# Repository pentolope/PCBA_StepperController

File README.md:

# Quiet Stepper Motor Controller

Single-axis stepper controller using a modern quiet microstepping driver and a small MCU, from a 12–24 V supply at 1.5 A RMS/phase minimum.

`PCBA_StepperController` is a single-axis stepper motor controller built around a modern quiet microstepping driver (the brief offers "a Trinamic-class device" as an example, not a mandate) and a small MCU. The brief fixes the supply range (12–24 V), the phase current target (1.5 A RMS/phase minimum), the presence of current-sense resistors and bulk/ceramic decoupling, STEP/DIR plus UART/SPI configuration access, fault/status signals, and a 4-pin motor connector; it also directs specific attention to driver thermal-pad grounding, high-current phase loops, and keeping current-sense routing away from switching nodes. Everything else — the actual driver and MCU parts, the logic rail, sense-resistor values, connector families, board outline, stackup details, protection and thermal strategy — is left to the design agent. At detail 3/5 this is a mid-specificity brief: the electrical envelope and the layout hazards are named, the implementation is not.

> **This board has not been designed.** There is no schematic, no layout and no
> part selection here — only the brief, a reading of the brief, and the
> scaffolding a design run needs. That is the intended state of this repository,
> not a gap in it.

## What the brief fixes, and what it leaves open

The brief pins down 16 requirements and deliberately leaves
19 decisions to whoever designs the board. The `Source` column says
which is which: `brief` is quoted from [BRIEF.md](BRIEF.md), `metadata` comes
from the benchmark catalogue, and `open` means the brief does not fix it.

| Aspect | Value | Source |
|---|---|---|
| Function | Single-axis stepper controller | brief |
| Motor driver | A modern quiet microstepping driver; a Trinamic-class device is given as an example only, not a mandated part | brief |
| Controller | A small MCU on the board | brief |
| Input supply | 12–24 V | brief |
| Motor current target | 1.5 A RMS/phase minimum | brief |
| Sensing and decoupling | Current-sense resistors plus bulk/ceramic decoupling (values and technologies not fixed) | brief |
| Control and configuration interfaces | STEP/DIR, and UART/SPI configuration access | brief |
| Fault/status | Fault/status signals present (form not fixed) | brief |
| Motor connector | 4-pin (family, pitch and rating not fixed) | brief |
| Layout emphasis called out by the brief | Driver thermal-pad grounding, high-current phase loops, current-sense routing kept away from switching nodes | brief |
| Likely layer count | 4 preferred | metadata |
| Category / difficulty / brief detail | motor-control, difficulty 3, detail 3 | metadata |
| Primary stressors | motor-current routing, driver thermal pad, sense resistors, mixed-signal grounding | metadata |
| Board outline, size, mounting and power-input connector | Not fixed by the brief — design agent's choice | open |

The full split, with the verbatim brief text substantiating every fixed
requirement, is in [board/requirements.md](board/requirements.md) and
machine-readably in [board/requirements.json](board/requirements.json).

**Missing details are design freedom, not permission to fabricate unstated user
requirements.** A choice the brief left open is recorded as a decision, with its
reasoning — never promoted into a requirement.

## Benchmark position

| | |
|---|---|
| Benchmark id | 8 of 32 |
| Category | motor-control |
| Difficulty | 3 / 5 |
| Brief detail | 3 / 5 |
| Likely layer count | 4 preferred |
| Primary stressors | motor-current routing, driver thermal pad, sense resistors, mixed-signal grounding |

This is a motor-control board at difficulty 3/5 and detail 3/5: it tests whether an agent can carry a modest power stage from a stated current and supply envelope through conductor sizing, sense-resistor design and a defensible thermal path, rather than drawing a schematic that only looks right. The four named stressors — motor-current routing, driver thermal pad, sense resistors, mixed-signal grounding — are all layout-and-substantiation problems, so what separates a strong result from a plausible-looking one is whether the physical implementation and its supporting calculations agree. Because the brief names an example device class rather than a part, it also probes whether the agent treats an illustrative example as a requirement.

This repository is one of thirty-two. The suite, the protocol and the results
live in [PCBA_AutoDesignAndTest_Bench](https://github.com/pentolope/PCBA_AutoDesignAndTest_Bench).

## Repository layout

| Path | Contents |
|---|---|
| `BRIEF.md` | the supplied brief — authoritative, preserved byte for byte, never edited |
| `board/requirements.md` | what the brief fixes, what it leaves open, and where decisions get recorded |
| `board/requirements.json` | the same split, machine-readable, each fixed requirement bound to brief text |
| `board/manifest.template.json` | the toolkit's minimum manifest, pre-filled for this board |
| `board/toolchain.json` | where this board's build finds KiCad and the router |
| `benchmark/metadata.json` | the supplied catalogue entry — category, difficulty, detail, stressors |
| `docs/architecture.md` | the decisions this board must make, as questions, unanswered |
| `docs/sources.md` | the classes of evidence the design will have to cite |
| `docs/status.md` | what exists, what does not, and what is deliberately absent |
| `candidates/` | disposable search output, ignored by Git |
| `.claude/skills/` | the accountability-review skill [CLAUDE.md](CLAUDE.md) requires before a push |
| `tooling/PCBA_AutoDesignAndTest` | the shared verification/routing/release toolkit, as a pinned submodule |

## Getting the repository

The toolkit is a submodule and carries KiCad Routing Tools as a submodule of its
own, so clone recursively:

```bash
git clone --recursive https://github.com/pentolope/PCBA_StepperController.git
```

```bash
git submodule update --init --recursive
```

## Designing the board

Generic verification, routing and release logic is **not** written here. It is
consumed from `tooling/PCBA_AutoDesignAndTest`, which is board-agnostic by
construction and must stay that way; this repository owns the board and nothing
else. Start from
[the toolkit's onboarding guide](tooling/PCBA_AutoDesignAndTest/examples/onboarding.md),
and see [CLAUDE.md](CLAUDE.md) for the rules a design run works under.

```bash
python3 tooling/PCBA_AutoDesignAndTest/run.py preflight
```

## Brief integrity

`BRIEF.md` SHA-256 `eb32e622a2161815c687ef267615287b89c1135211a0c5d5494930910a460444`

Every quotation in `board/requirements.json` is bound to those exact bytes. If
the brief ever changes, the bindings are stale by construction — which is the
point of recording the digest.

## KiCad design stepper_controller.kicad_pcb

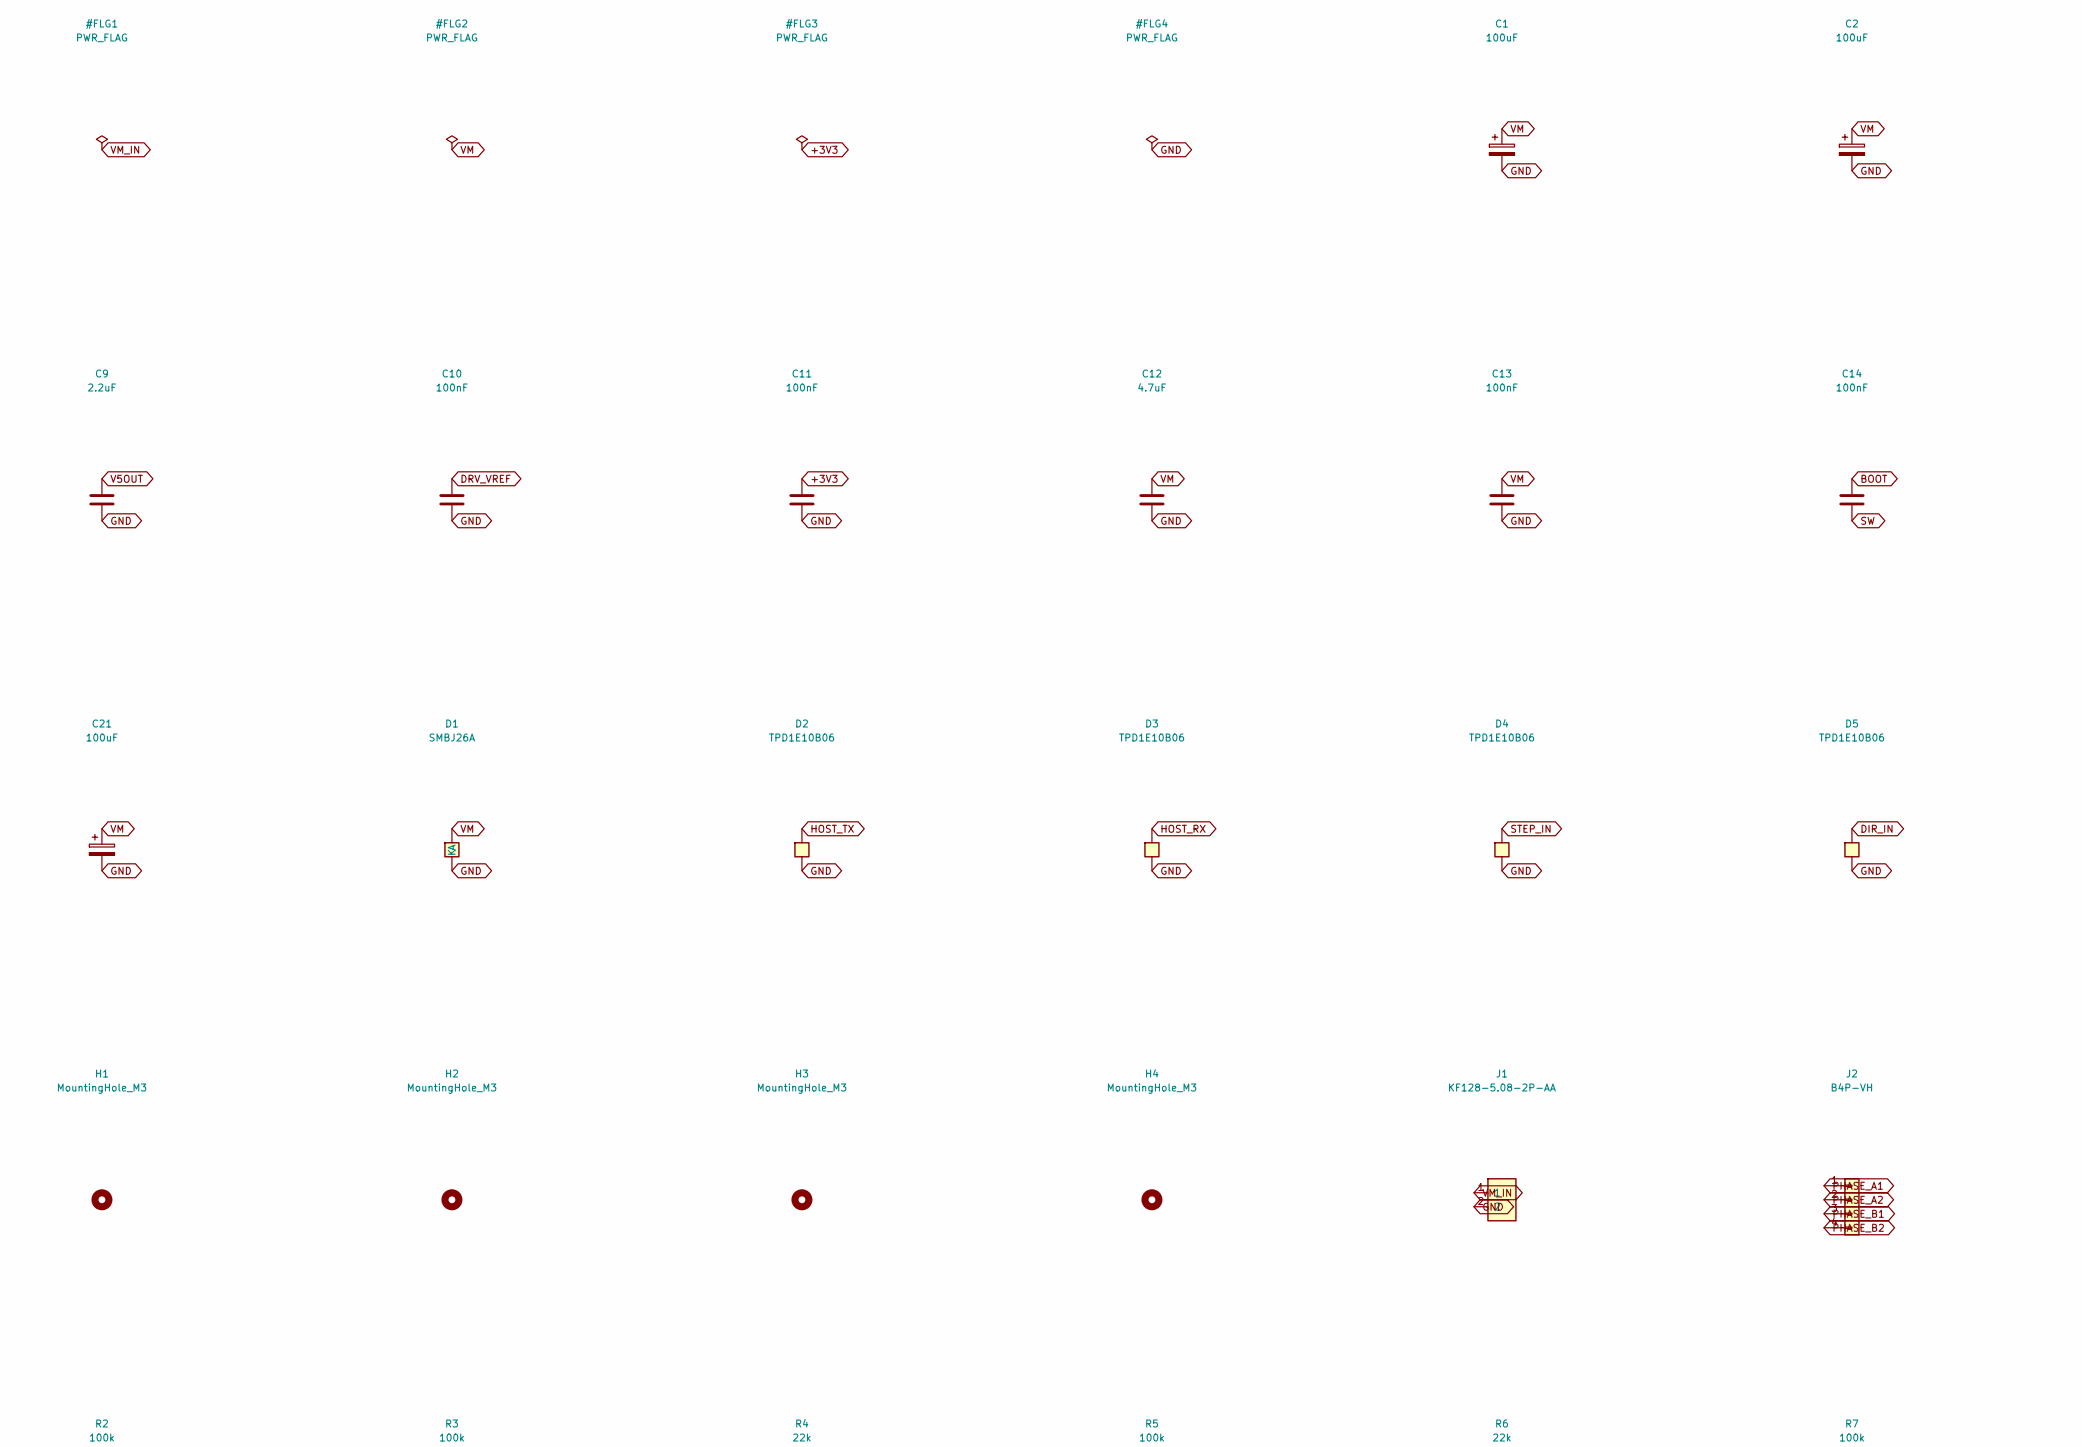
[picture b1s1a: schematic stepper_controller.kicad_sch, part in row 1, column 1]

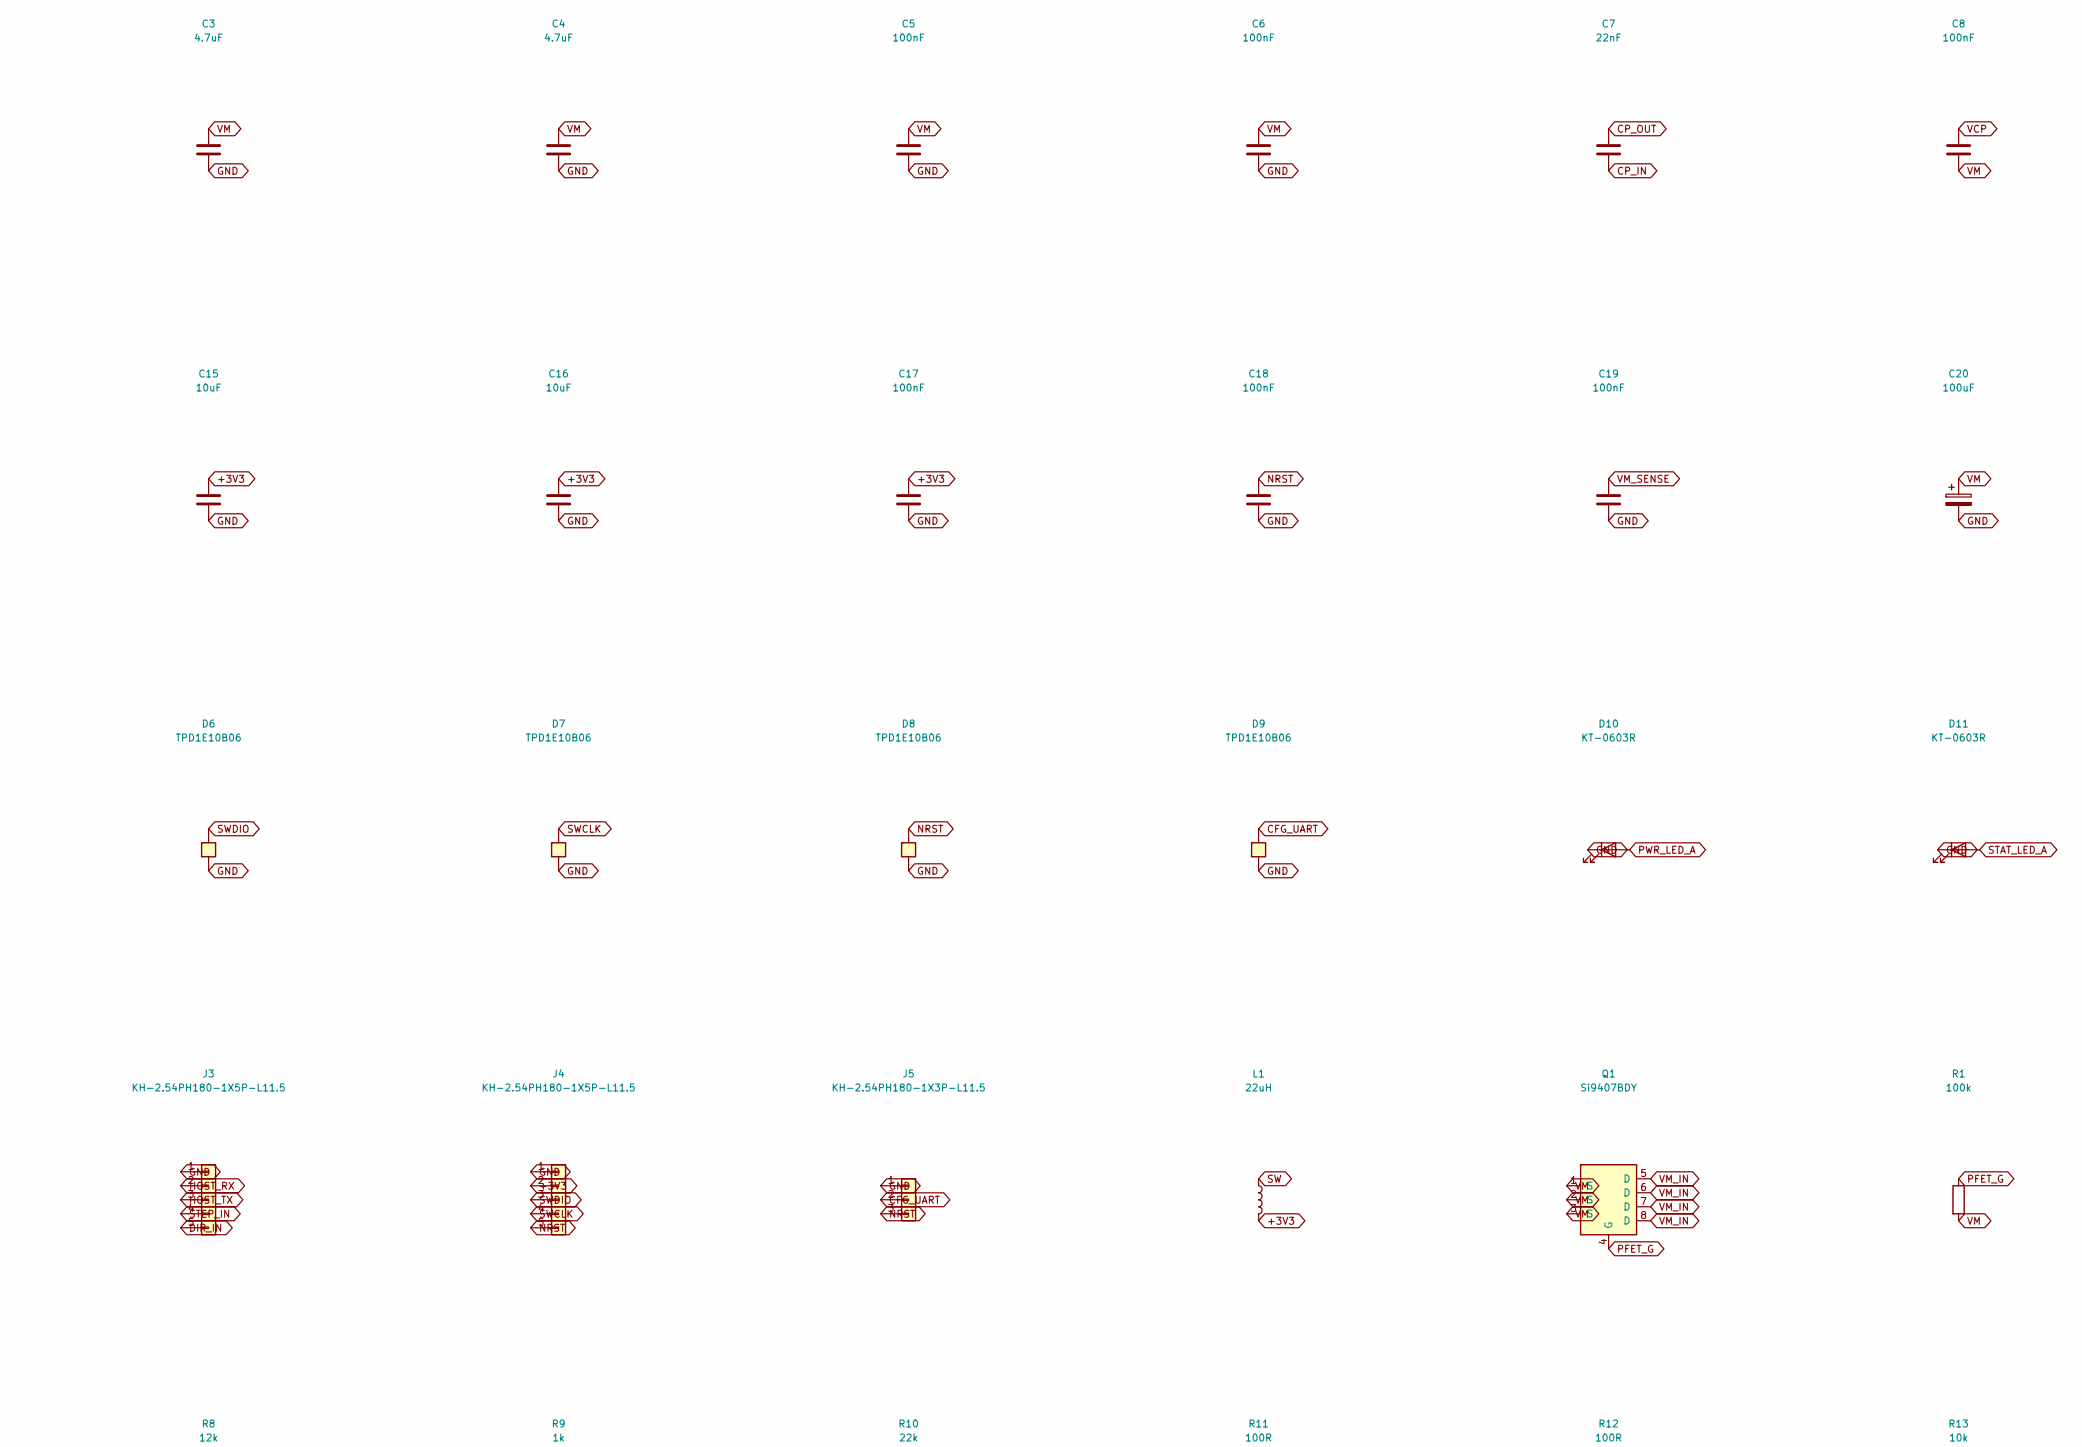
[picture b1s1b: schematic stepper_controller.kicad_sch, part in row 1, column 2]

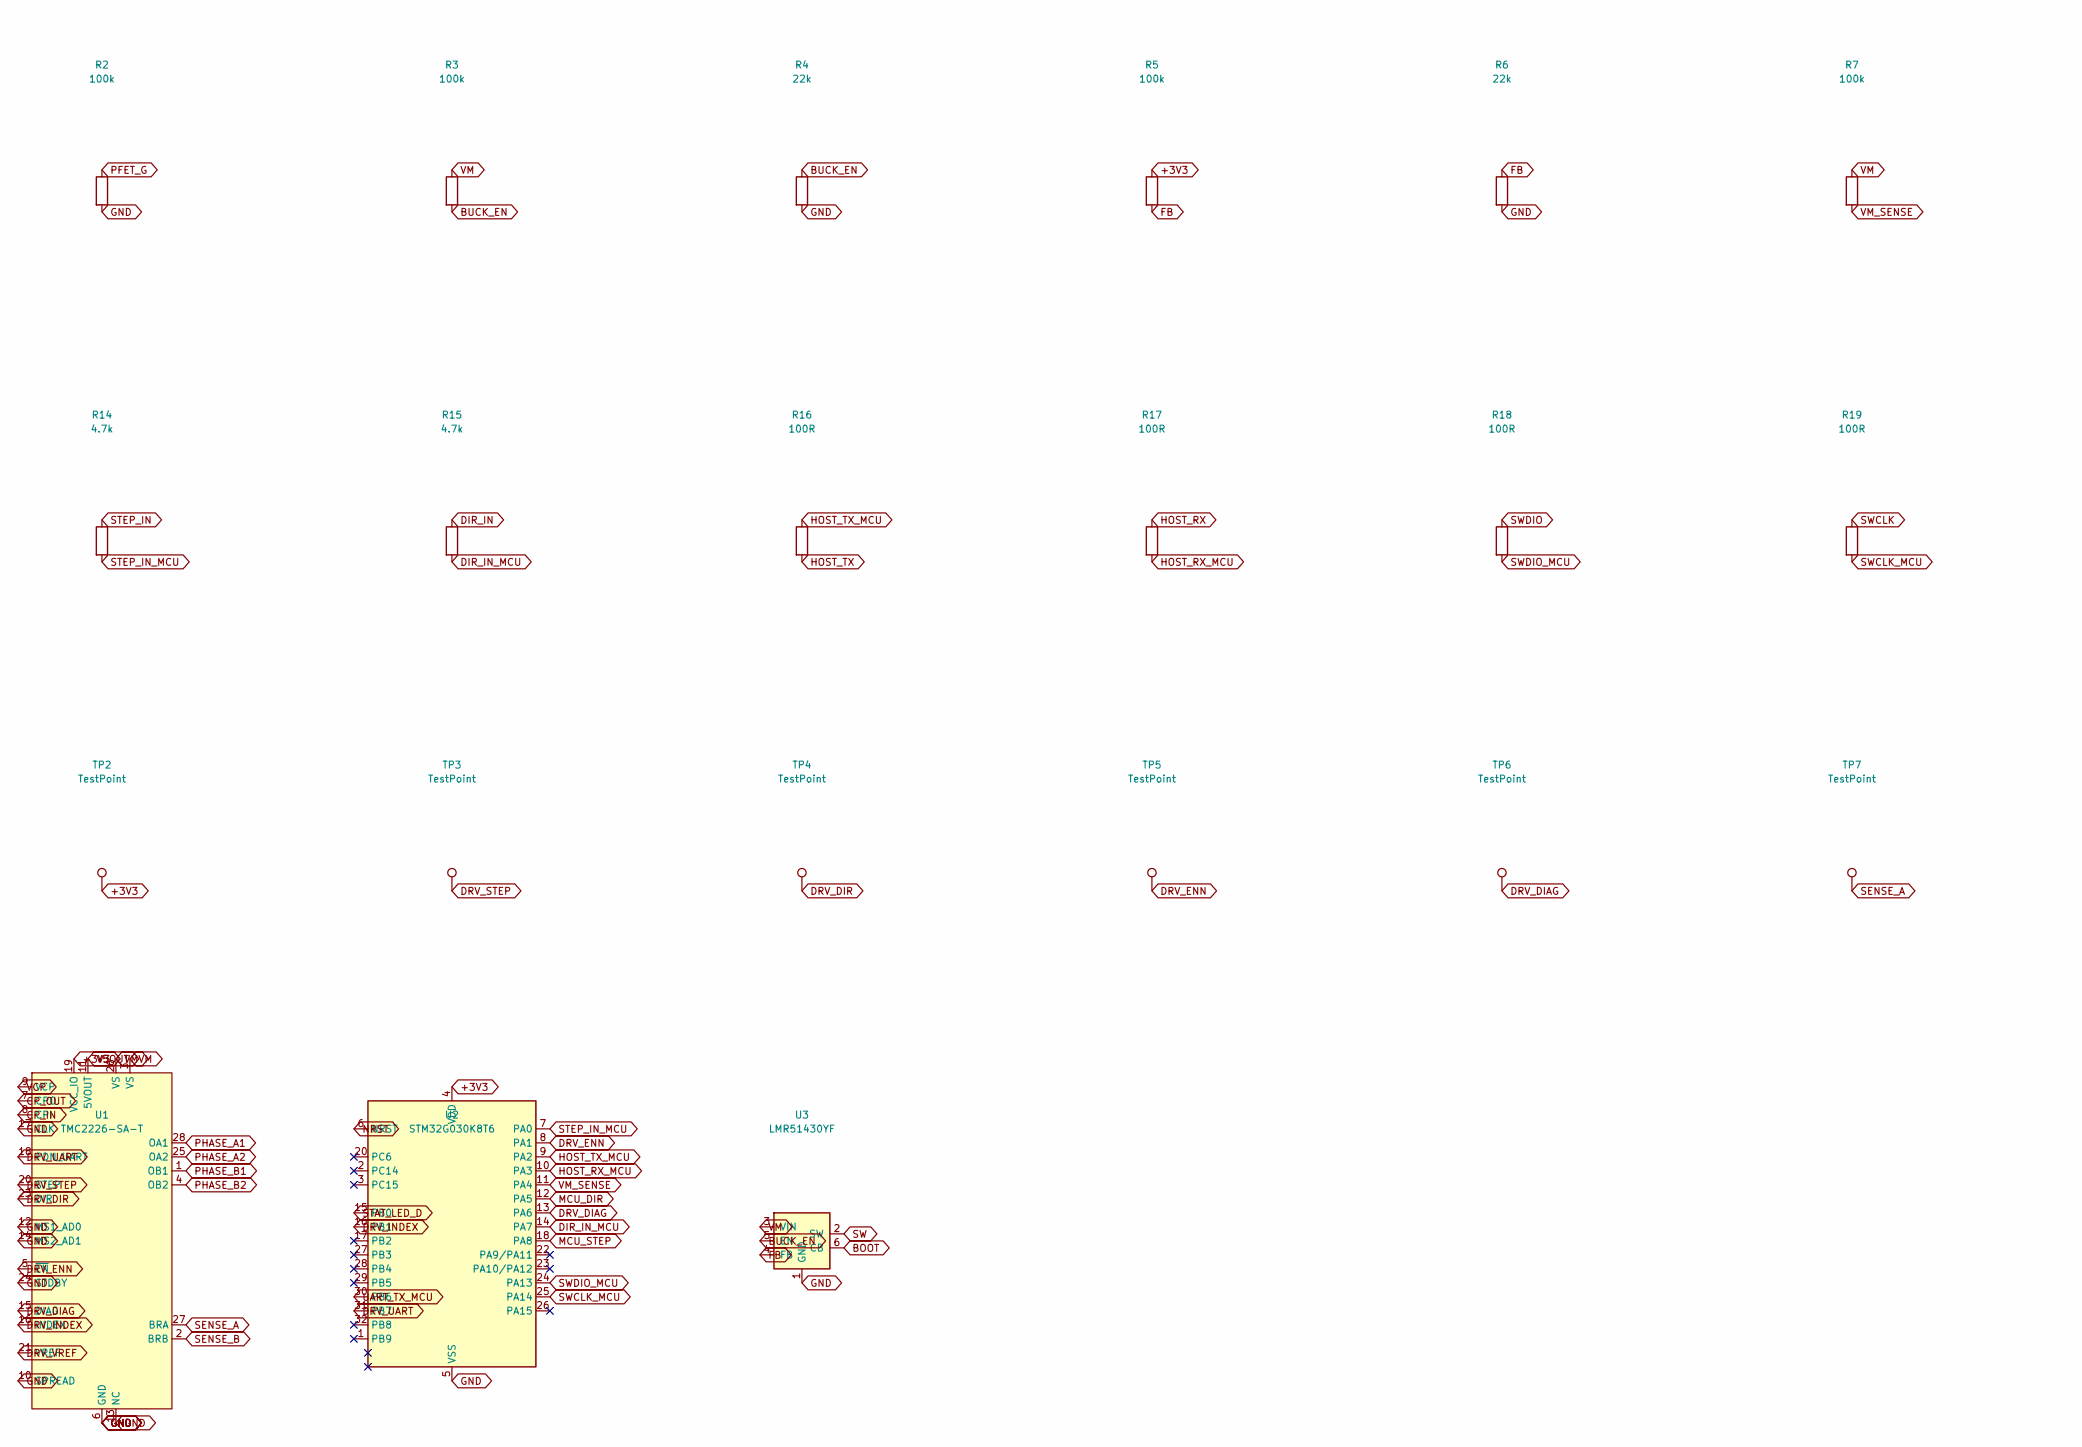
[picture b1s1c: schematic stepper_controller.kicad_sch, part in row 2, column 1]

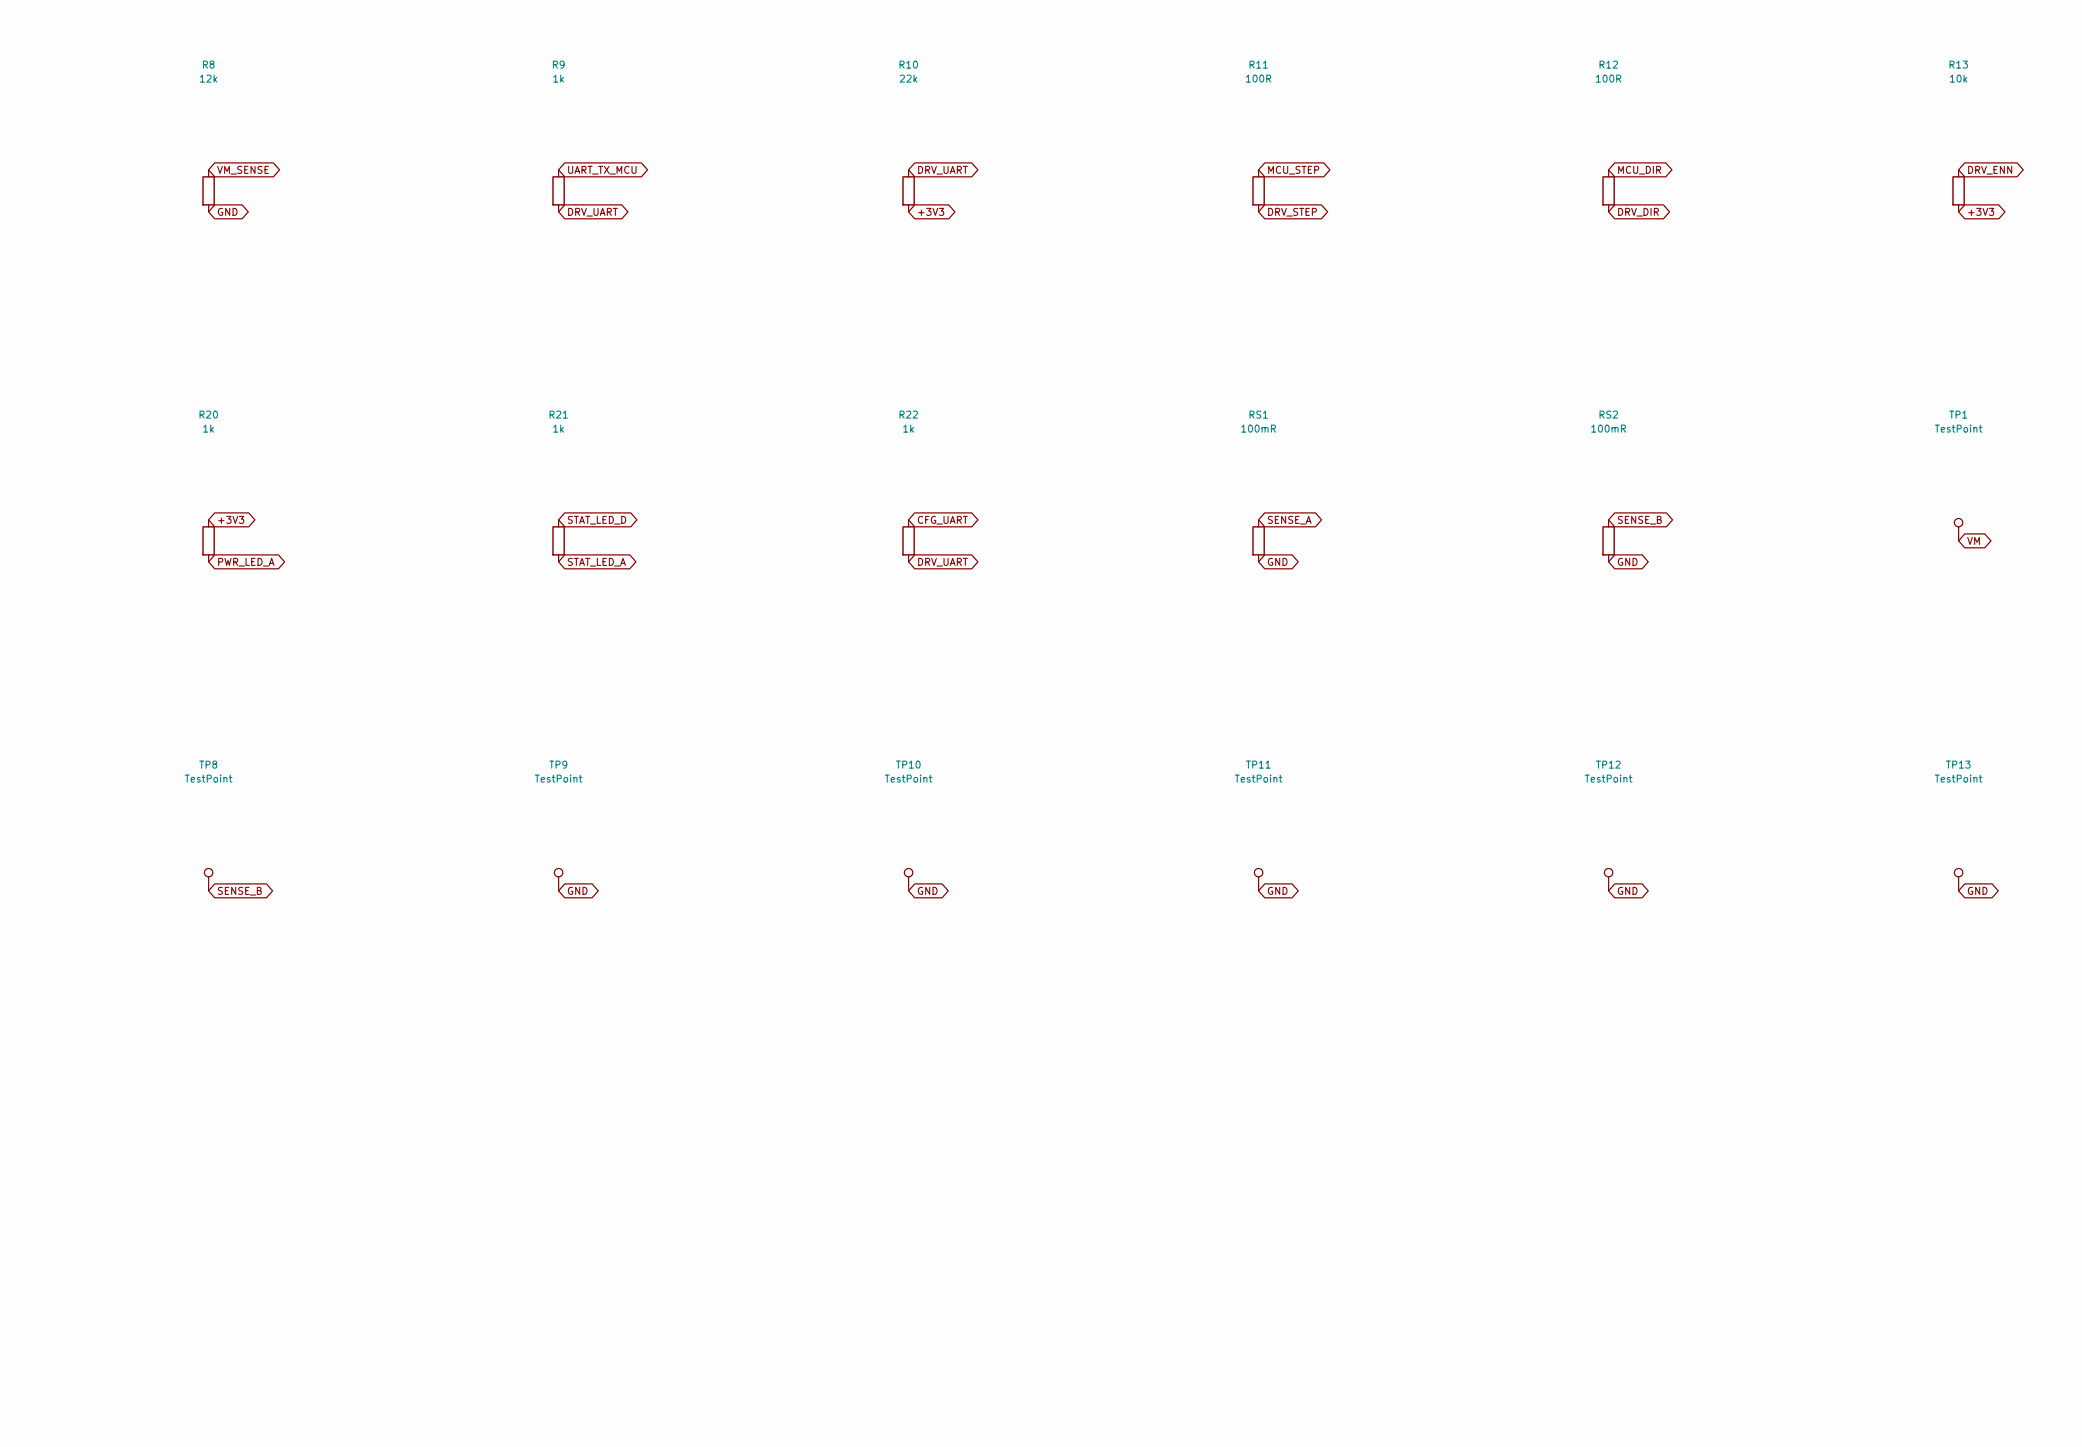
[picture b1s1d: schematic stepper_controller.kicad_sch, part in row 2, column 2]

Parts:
C1, C2, C20, C21: 100uF; CP_Elec_10x10.5; MPN HHXC500ARA101MJA0G; LCSC C3008515
C3, C4, C12: 4.7uF; C_1206_3216Metric; MPN CC1206KKX7R9BB475; LCSC C132170
C5, C6, C8, C10, C11, C13, C14, C17, C18, C19: 100nF; C_0603_1608Metric; MPN CC0603KRX7R0BB104; LCSC C113803
C7: 22nF; C_0603_1608Metric; MPN CC0603KRX7R9BB223; LCSC C106222
C9: 2.2uF; C_0805_2012Metric; MPN CC0805KKX7R8BB225; LCSC C277470
C15, C16: 10uF; C_0805_2012Metric; MPN CC0805KKX7R7BB106; LCSC C326595
D1: SMBJ26A; D_SMB; MPN SMBJ26A; LCSC C315992
D2, D3, D4, D5, D6, D7, D8, D9: TPD1E10B06; TI_X1SON-2_1.0x0.6mm_P0.65mm; MPN TPD1E10B06DPYR; LCSC C48260
D10, D11: KT-0603R; LED_0603_1608Metric; MPN KT-0603R; LCSC C2286
H1, H2, H3, H4: MountingHole_M3; MountingHole_3.2mm_M3
J1: KF128-5.08-2P-AA; TerminalBlock_KF128-5.08_1x02_P5.08mm; MPN KF128-5.08-2P-AA; LCSC C474952
J2: B4P-VH; JST_VH_B4P-VH_1x04_P3.96mm_Vertical; MPN B4P-VH(LF)(SN); LCSC C160317
J3, J4: KH-2.54PH180-1X5P-L11.5; PinHeader_1x05_P2.54mm_Vertical; MPN KH-2.54PH180-1X5P-L11.5; LCSC C2932699
J5: KH-2.54PH180-1X3P-L11.5; PinHeader_1x03_P2.54mm_Vertical; MPN KH-2.54PH180-1X3P-L11.5; LCSC C2932698
L1: 22uH; L_Bourns_SRP4020TA; MPN SRP4020TA-220M; LCSC C1847949
Q1: Si9407BDY; SOIC-8_3.9x4.9mm_P1.27mm; MPN Si9407BDY-T1-GE3; LCSC C141567
R1, R2, R3, R5, R7: 100k; R_0603_1608Metric; MPN 0603WAF1003T5E; LCSC C25803
R4, R6, R10: 22k; R_0603_1608Metric; MPN 0603WAF2202T5E; LCSC C31850
R8: 12k; R_0603_1608Metric; MPN 0603WAF1202T5E; LCSC C22790
R9, R20, R21, R22: 1k; R_0603_1608Metric; MPN 0603WAF1001T5E; LCSC C21190
R11, R12, R16, R17, R18, R19: 100R; R_0603_1608Metric; MPN 0603WAF1000T5E; LCSC C22775
R13: 10k; R_0603_1608Metric; MPN 0603WAF1002T5E; LCSC C25804
R14, R15: 4.7k; R_0603_1608Metric; MPN 0603WAF4701T5E; LCSC C23162
RS1, RS2: 100mR; R_1206_3216Metric; MPN HoLRTX1206-1W-100mR-1%; LCSC C5123673
TP1, TP2, TP3, TP4, TP5, TP6, TP7, TP8, TP9, TP10, TP11, TP12, TP13: TestPoint; TestPoint_Pad_D1.0mm
U1: TMC2226-SA-T; HTSSOP-28-1EP_4.4x9.7mm_P0.65mm_EP2.75x6.2mm_SegmentedMask; MPN TMC2226-SA-T; LCSC C705366
U2: STM32G030K8T6; LQFP-32_7x7mm_P0.8mm; MPN STM32G030K8T6TR; LCSC C724044
U3: LMR51430YF; SOT-23-6; MPN LMR51430YFDDCR; LCSC C5219261

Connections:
+3V3: C11.1, C15.1, C16.1, C17.1, J4.2, L1.2, R5.1, R10.2, R13.2, R20.1, TP2.1, U1.19 (VCC_IO), U2.4 (VDD)
BOOT: C14.1, U3.6 (CB)
BUCK_EN: R3.2, R4.1, U3.5 (EN)
CFG_UART: D9.1 (IO1), J5.2, R22.1
CP_IN: C7.2, U1.8 (CPI)
CP_OUT: C7.1, U1.7 (CPO)
DIR_IN: D5.1 (IO1), J3.5, R15.1
DIR_IN_MCU: R15.2, U2.14 (PA7)
DRV_DIAG: TP6.1, U1.15 (DIAG), U2.13 (PA6)
DRV_DIR: R12.2, TP4.1, U1.23 (DIR)
DRV_ENN: R13.1, TP5.1, U1.5 (~EN), U2.8 (PA1)
DRV_INDEX: U1.16 (INDEX), U2.16 (PB1)
DRV_STEP: R11.2, TP3.1, U1.20 (STEP)
DRV_UART: R9.2, R10.1, R22.2, U1.18 (PDN_UART), U2.31 (PB7)
DRV_VREF: C10.1, U1.21 (VREF)
FB: R5.2, R6.1, U3.4 (FB)
GND: C1.2, C2.2, C3.2, C4.2, C5.2, C6.2, C9.2, C10.2, C11.2, C12.2, C13.2, C15.2, C16.2, C17.2, C18.2, C19.2, C20.2, C21.2, D1.2 (A), D2.2 (IO2), D3.2 (IO2), D4.2 (IO2), D5.2 (IO2), D6.2 (IO2), D7.2 (IO2), D8.2 (IO2), D9.2 (IO2), D10.1 (K), D11.1 (K), J1.2, J3.1, J4.1, J5.1, R2.2, R4.2, R6.2, R8.2, RS1.2, RS2.2, TP9.1, TP10.1, TP11.1, TP12.1, TP13.1, U1.6 (GND), U1.10 (SPREAD), U1.12 (MS1_AD0), U1.13 (NC), U1.14 (MS2_AD1), U1.17 (CLK), U1.22 (GND), U1.24 (STDBY), U1.29 (GND), U2.5 (VSS), U3.1 (GND)
HOST_RX: D3.1 (IO1), J3.2, R17.1
HOST_RX_MCU: R17.2, U2.10 (PA3)
HOST_TX: D2.1 (IO1), J3.3, R16.2
HOST_TX_MCU: R16.1, U2.9 (PA2)
MCU_DIR: R12.1, U2.12 (PA5)
MCU_STEP: R11.1, U2.18 (PA8)
NRST: C18.1, D8.1 (IO1), J4.5, J5.3, U2.6 (NRST)
PFET_G: Q1.4 (G), R1.1, R2.1
PHASE_A1: J2.1, U1.28 (OA1)
PHASE_A2: J2.2, U1.25 (OA2)
PHASE_B1: J2.3, U1.1 (OB1)
PHASE_B2: J2.4, U1.4 (OB2)
PWR_LED_A: D10.2 (A), R20.2
SENSE_A: RS1.1, TP7.1, U1.27 (BRA)
SENSE_B: RS2.1, TP8.1, U1.2 (BRB)
STAT_LED_A: D11.2 (A), R21.2
STAT_LED_D: R21.1, U2.15 (PB0)
STEP_IN: D4.1 (IO1), J3.4, R14.1
STEP_IN_MCU: R14.2, U2.7 (PA0)
SW: C14.2, L1.1, U3.2 (SW)
SWCLK: D7.1 (IO1), J4.4, R19.1
SWCLK_MCU: R19.2, U2.25 (PA14)
SWDIO: D6.1 (IO1), J4.3, R18.1
SWDIO_MCU: R18.2, U2.24 (PA13)
UART_TX_MCU: R9.1, U2.30 (PB6)
V5OUT: C9.1, U1.11 (5VOUT)
VCP: C8.1, U1.9 (VCP)
VM: C1.1, C2.1, C3.1, C4.1, C5.1, C6.1, C8.2, C12.1, C13.1, C20.1, C21.1, D1.1 (K), Q1.1 (S), Q1.2 (S), Q1.3 (S), R1.2, R3.1, R7.1, TP1.1, U1.3 (VS), U1.26 (VS), U3.3 (VIN)
VM_IN: J1.1, Q1.5 (D), Q1.6 (D), Q1.7 (D), Q1.8 (D)
VM_SENSE: C19.1, R7.2, R8.1, U2.11 (PA4)

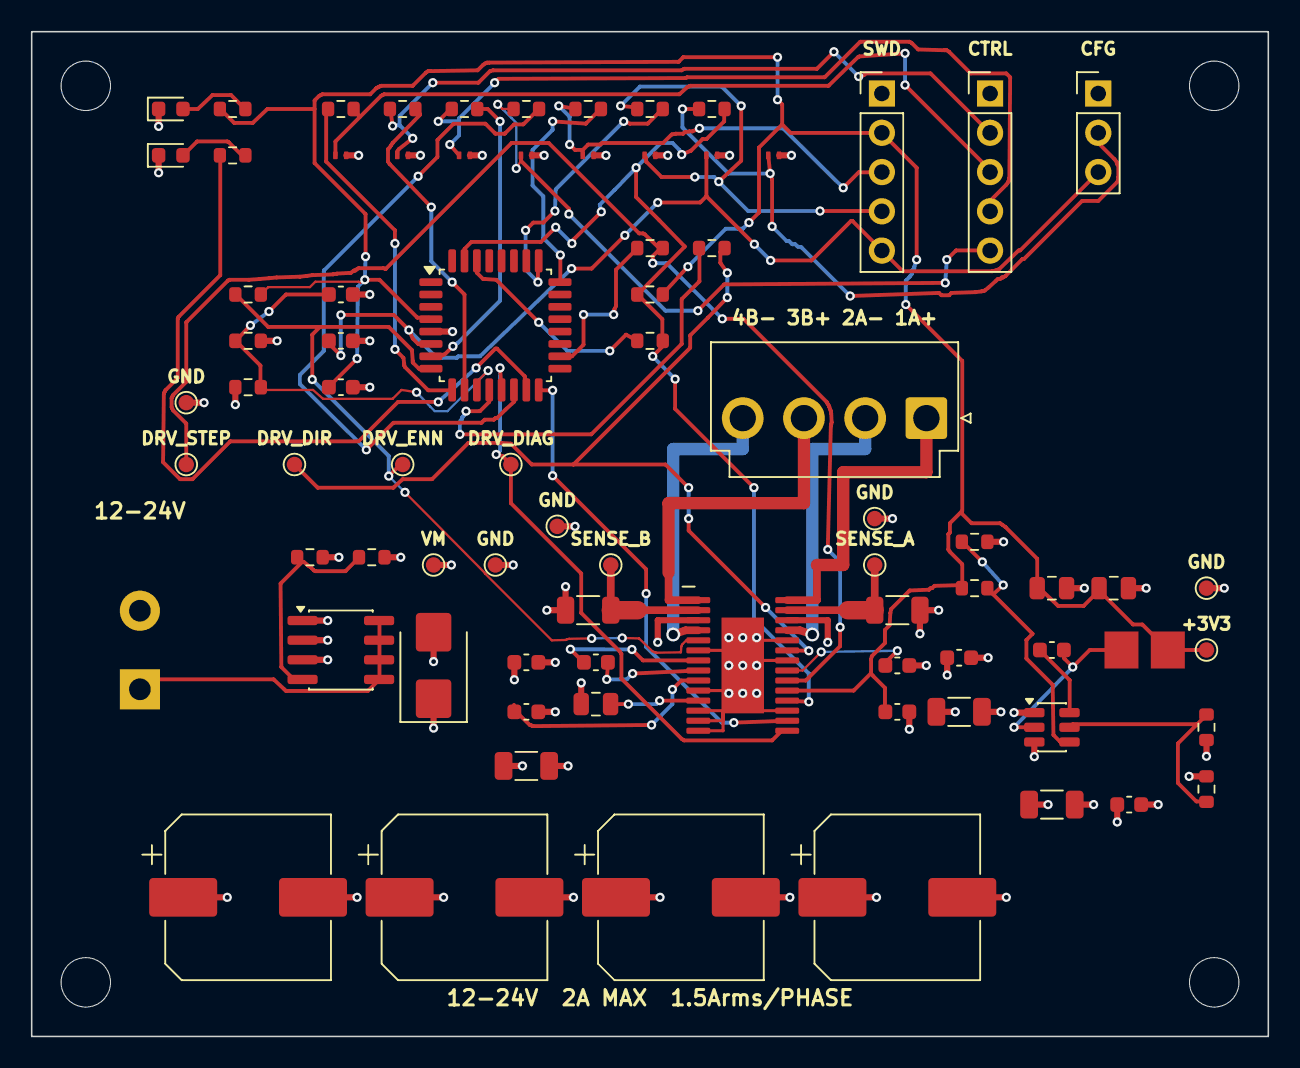
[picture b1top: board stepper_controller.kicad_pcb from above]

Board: 4 copper layers, 80.0 x 65.0 mm, 83 parts (0 on the bottom side), 47 nets.

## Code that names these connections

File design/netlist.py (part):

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
MCU_PINS = {
    "PB9": "1", "PC14": "2", "PC15": "3", "VDD": "4", "VSS": "5",
    "NRST": "6", "PA0": "7", "PA1": "8", "PA2": "9", "PA3": "10",
    "PA4": "11", "PA5": "12", "PA6": "13", "PA7": "14", "PB0": "15",
    "PB1": "16", "PB2": "17", "PA8": "18", "NC_PA9": "19", "PC6": "20",
    "NC_PA10": "21", "PA11": "22", "PA12": "23", "PA13": "24",
    "PA14": "25", "PA15": "26", "PB3": "27", "PB4": "28", "PB5": "29",
    "PB6": "30", "PB7": "31", "PB8": "32",
}

#: Controller pin -> net, and the peripheral each assignment relies on.
MCU_FUNCTION = {
    "PA0": ("STEP_IN_MCU", "EXTI0"),
    "PA1": ("DRV_ENN", "GPIO"),
    "PA2": ("HOST_TX_MCU", "USART2_TX"),
    "PA3": ("HOST_RX_MCU", "USART2_RX"),
    "PA4": ("VM_SENSE", "ADC_IN4"),
    "PA5": ("MCU_DIR", "GPIO"),
    "PA6": ("DRV_DIAG", "EXTI6"),
    "PA7": ("DIR_IN_MCU", "GPIO"),
    "PB0": ("STAT_LED_D", "GPIO"),
    "PB1": ("DRV_INDEX", "GPIO"),
    "PA8": ("MCU_STEP", "TIM1_CH1"),
    "PA13": ("SWDIO_MCU", "SWDIO"),
    "PA14": ("SWCLK_MCU", "SWCLK"),
    "PB6": ("UART_TX_MCU", "USART1_TX"),
    "PB7": ("DRV_UART", "USART1_RX"),
    "VDD": ("+3V3", "supply"),
    "VSS": ("GND", "supply"),
    "NRST": ("NRST", "reset"),
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#: Pins the datasheet's injection-susceptibility table gives no negative
#: injection tolerance at all.
MCU_NO_NEGATIVE_INJECTION_PINS = {
    "8": "PA1", "12": "PA5", "16": "PB1", "17": "PB2", "24": "PA13",
    "32": "PB8",
}

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        "VM_IN": supply_input,
        "VM": motor_rail,
        "+3V3": logic_rail,
        "PFET_G": ["Q1.%s" % PFET_GATE_PIN, "R1.1", "R2.1"],
        "BUCK_EN": [_buck_pin("EN"), "R3.2", "R4.1"],
        "SW": [_buck_pin("SW"), "L1.1", "C14.2"],
        "BOOT": [_buck_pin("CB"), "C14.1"],
        "FB": [_buck_pin("FB"), "R5.2", "R6.1"],
        "VM_SENSE": [_mcu_net_pin("VM_SENSE"), "R7.2", "R8.1", "C19.1"],
        "V5OUT": [_driver_pin("V5OUT"), "C9.1"],
        "VCP": [_driver_pin("VCP"), "C8.1"],
        "CP_OUT": [_driver_pin("CPO"), "C7.1"],
        "CP_IN": [_driver_pin("CPI"), "C7.2"],
        "DRV_VREF": [_driver_pin("VREF"), "C10.1"],
        "PHASE_A1": [_driver_pin("OA1"),
                     "J2.%d" % MOTOR_CONNECTOR_PINS["A1"]],
        "PHASE_A2": [_driver_pin("OA2"),
                     "J2.%d" % MOTOR_CONNECTOR_PINS["A2"]],
        "PHASE_B1": [_driver_pin("OB1"),
                     "J2.%d" % MOTOR_CONNECTOR_PINS["B1"]],
        "PHASE_B2": [_driver_pin("OB2"),
                     "J2.%d" % MOTOR_CONNECTOR_PINS["B2"]],
        "SENSE_A": [_driver_pin("BRA"), "RS1.1", "TP7.1"],
        "SENSE_B": [_driver_pin("BRB"), "RS2.1", "TP8.1"],
        "DRV_ENN": [_driver_pin("ENN"), _mcu_net_pin("DRV_ENN"),
                    "R13.1", "TP5.1"],
        "DRV_DIAG": [_driver_pin("DIAG"), _mcu_net_pin("DRV_DIAG"), "TP6.1"],
        "DRV_INDEX": [_driver_pin("INDEX"), _mcu_net_pin("DRV_INDEX")],
        "DRV_STEP": [_driver_pin("STEP"), "R11.2", "TP3.1"],
        "DRV_DIR": [_driver_pin("DIR"), "R12.2", "TP4.1"],
        "MCU_STEP": [_mcu_net_pin("MCU_STEP"), "R11.1"],
        "MCU_DIR": [_mcu_net_pin("MCU_DIR"), "R12.1"],
        "DRV_UART": [_driver_pin("PDN_UART"), _mcu_net_pin("DRV_UART"), "R9.2",
                     "R10.1", "R22.2"],
        "CFG_UART": ["R22.1", "D9.1", "J5.2"],
        "UART_TX_MCU": [_mcu_net_pin("UART_TX_MCU"), "R9.1"],
        "HOST_TX_MCU": [_mcu_net_pin("HOST_TX_MCU"), "R16.1"],
        "HOST_TX": ["R16.2", "D2.1", "J3.3"],
        "HOST_RX_MCU": [_mcu_net_pin("HOST_RX_MCU"), "R17.2"],
        "HOST_RX": ["R17.1", "D3.1", "J3.2"],
        "STEP_IN": ["R14.1", "D4.1", "J3.4"],
        "STEP_IN_MCU": [_mcu_net_pin("STEP_IN_MCU"), "R14.2"],
        "DIR_IN": ["R15.1", "D5.1", "J3.5"],
        "DIR_IN_MCU": [_mcu_net_pin("DIR_IN_MCU"), "R15.2"],
        "SWDIO": ["R18.1", "D6.1", "J4.3"],
        "SWDIO_MCU": [_mcu_net_pin("SWDIO_MCU"), "R18.2"],
        "SWCLK": ["R19.1", "D7.1", "J4.4"],
        "SWCLK_MCU": [_mcu_net_pin("SWCLK_MCU"), "R19.2"],
        "NRST": [_mcu_net_pin("NRST"), "C18.1", "D8.1", "J4.5", "J5.3"],
        "PWR_LED_A": ["R20.2", "D10.2"],
        "STAT_LED_D": [_mcu_net_pin("STAT_LED_D"), "R21.1"],
        "STAT_LED_A": ["R21.2", "D11.2"],
    }
    return nets
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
